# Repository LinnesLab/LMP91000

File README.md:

# LMP91000
Arduino library for the LMP91000 AFE Potentiostat for Electrochemical Sensing

LMP91000 connections / Arduino Connections

DGND / GND  
MENB / GND  
SCL / SCL (with 10k pull-up resistor)  
SDA / SDA (with 10k pull-up resistor)  
VDD / 3.3V  
AGND / GND  
CE / Counter electrode  
RE / Reference electrode  
WE / Working electrode  
VREF / 3.3V  
C1 / not needed  
C2 / not needed  
Vout / Analog Input A0

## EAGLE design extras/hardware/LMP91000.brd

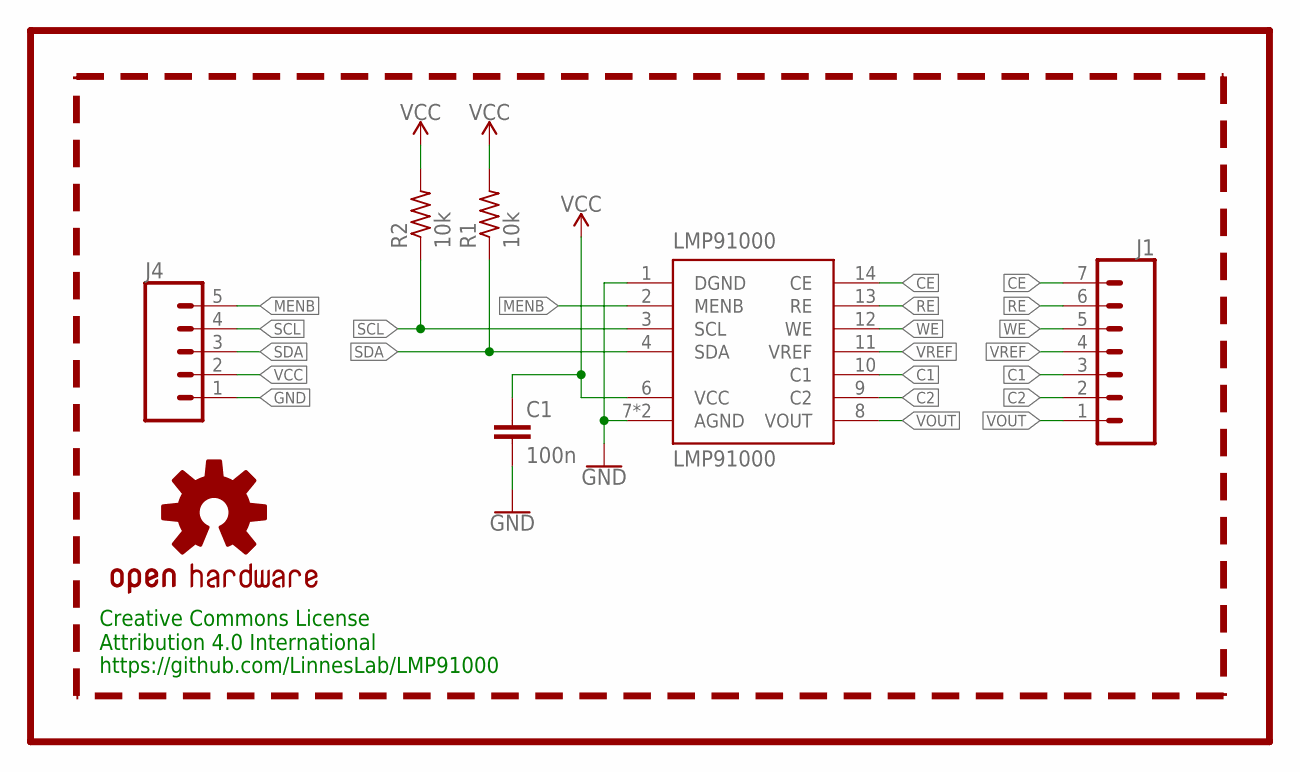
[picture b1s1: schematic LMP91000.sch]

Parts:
C1: 100n; C0402
J1: CONN_07NO_SILK; 1X07_NO_SILK
J4: CONN_05NO_SILK; 1X05_NO_SILK
LMP91000: LMP91000; WSON-14
LOGO1: OSHW-LOGOS; OSHW-LOGO-S
R1, R2: 10k; R0402-BIGGER
U$1: LINNES.LAB.05
U$2: LINNES.LAB.LOGO
U$3: REVISION.B; REV.B

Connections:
C1: J1.3, LMP91000.10 (C1)
C2: J1.2, LMP91000.9 (C2)
CE: J1.7, LMP91000.14 (CE)
GND: C1.2, J4.1, LMP91000.1 (DGND), LMP91000.7 (AGND), LMP91000.DAP (AGND)
MENB: J4.5, LMP91000.2 (MENB)
RE: J1.6, LMP91000.13 (RE)
SCL: J4.4, LMP91000.3 (SCL), R2.1
SDA: J4.3, LMP91000.4 (SDA), R1.1
VCC: C1.1, J4.2, LMP91000.6 (VCC), R1.2, R2.2
VOUT: J1.1, LMP91000.8 (VOUT)
VREF: J1.4, LMP91000.11 (VREF)
WE: J1.5, LMP91000.12 (WE)

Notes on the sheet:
Creative Commons License Attribution 4.0 International
https://github.com/LinnesLab/LMP91000

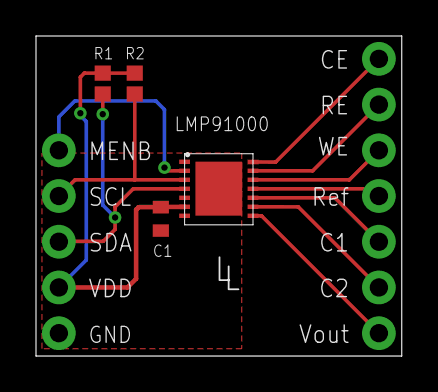
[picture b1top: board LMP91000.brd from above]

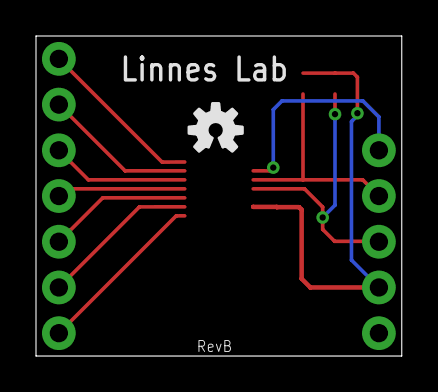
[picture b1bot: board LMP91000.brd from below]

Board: 2 copper layers, 20.3 x 17.8 mm, 10 parts (3 on the bottom side), 12 nets.

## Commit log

2018-06-19 added example sketch for running cyclic voltammetry
2018-06-19 updates to CyclicVoltammetry example to include settling time before measurements
2018-08-06 added keywords.txt file
2018-08-10 added a constant for the number of bias settings...also added an example for Chronoamperometry
2018-08-11 added another method to the LMP91000 class that allows changing the bias and the polarity of the bias simultaneously, also added an example for doing Normal Pulse Voltammetry
2018-08-28 Correct invalid keywords in keywords.txt
    Previously, some of the definitions were left on the keywords, causing them to not be recognized by the Arduino IDE.
2019-01-14 uploading breakout board design
2019-01-14 updated keywords.txt file
2019-01-19 made modifications to fit Arduino library Manager requirements and created extras folder for holding breakout board design
2019-01-19 deleted folders that don't need to be on repo
2019-01-19 deleting more things
2019-01-19 added lbirary properties file to upload to Arduino Library Manager
2019-01-19 removing more
2019-01-19 updated comments
2019-01-25 making some mods
2019-01-25 adding BOM and Gerbers
2019-01-26 really close to be exact with the VSP
2019-01-26 more updates
2019-01-31 confirmed cv forward and backward with AD5644R 14-bit DAC
2019-01-31 changed voltage tolerance from 1% to 0.75%
2019-01-31 got the INA and Diff amp working too..ina is the ad623 with no gain resistor...diff amp with mcp6002 with all resistors equal to 33k...both outputs reference to 1/2 vdd appropriately
2019-02-01 added first version of SWV with the AD5644R
2019-02-01 both SWV and CV appear to be working with the AD5644R in both forward adn reverse directions for positive and negative redox molecules
2019-02-01 used to get good data that resulted in file au3-probe-2019-02-01-1701.xlsx
2019-02-02 tested this with fecn and compared side by side with vsp-300...seemed to fit fine...may just need to switch to current to compare correctly
2019-04-09 CV using MiniStat Button Cell Rev A for measuring FeCN
2021-10-05 many updates
2023-03-10 Fix getVoltage. Requeres a reading from vOut
